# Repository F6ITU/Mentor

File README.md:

# Mentor

Kicad files

An Arduino based SSPA display controler for HPSDR/Hermes familly
This module controls 
- voltage
- current
- temperature
- VSWR/PWR
- cooling fan
- 4x40 lcd display
and shuts down the Bias current while beeping in case of dificulties

This board and the associated firmware have been developped by ON7EQ. 

http://www.qsl.net/on7eq/projects/arduino_sspa.htm

Some code modifications have been made by John Melton for 
the Hermes familly.

The design of this board uses the generic output names
used by all Hermes/Angelia boards and could directly be plugged 
on the Alexandrie control board

So far, NO SSPA and NO Reflectometer/Refl-fwd coupler have been
designed. A multipurpose 33dB Tandem Match coupler
is under development (for both VSWR/PWR measurement and 
predistorsion -aka "pure signal"- sampling)

Board's dimensions are oversized to fit the 5x10 and 10x10cm 
size of all board of the Hermes project under Kicad: 

AlexI2C

Alexandrie 

Alexiares_Coax_Out

Alexiares_HPF

Alexiares_LPF

Mentor(this one)

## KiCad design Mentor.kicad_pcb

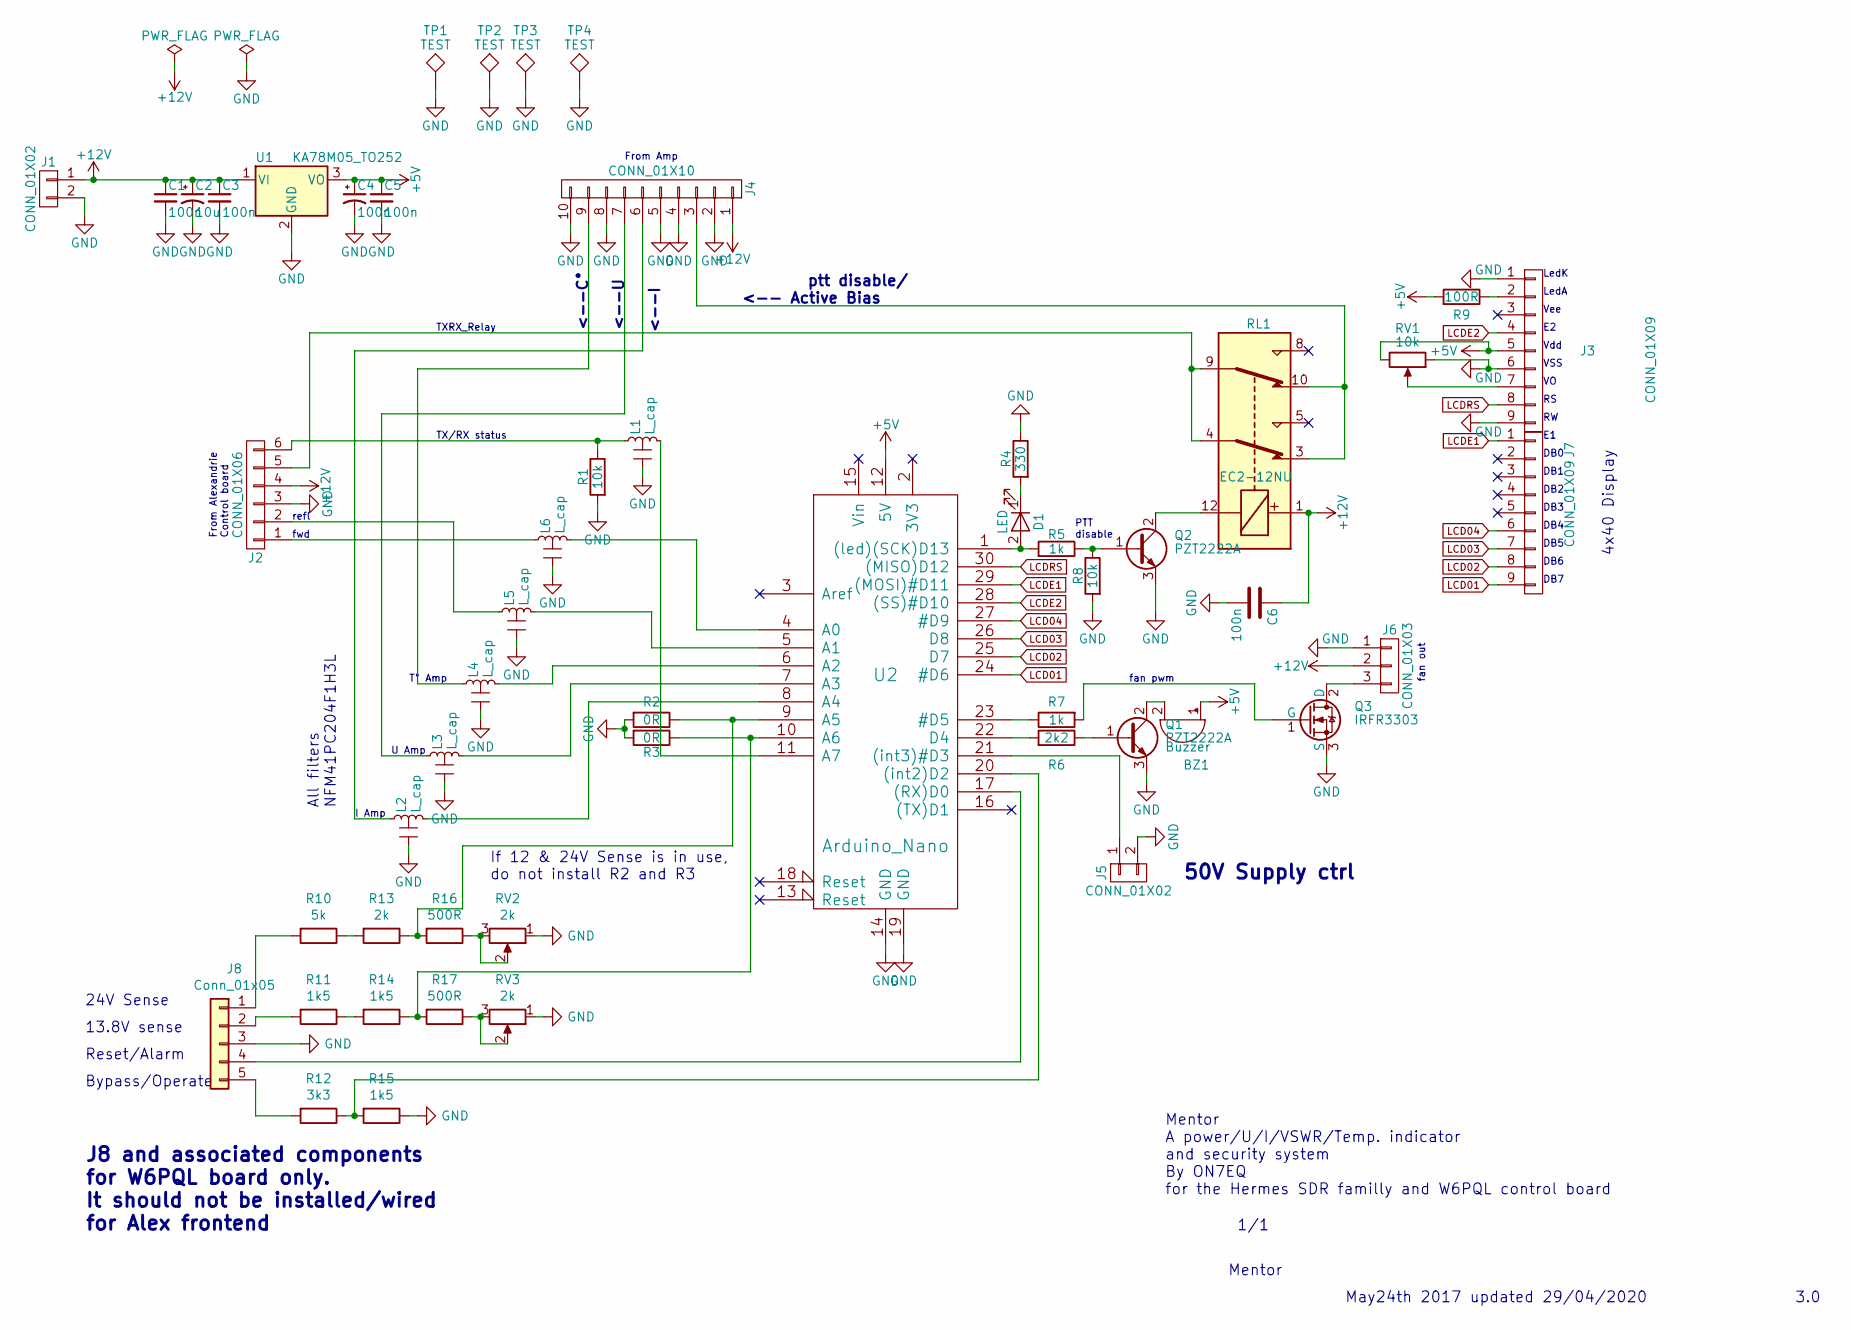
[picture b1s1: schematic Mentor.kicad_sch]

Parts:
BZ1: Buzzer; Buzzer_12x9.5RM7.6
C1, C3, C4, C5, C6: 100n; C_0805_2012Metric_Pad1.15x1.40mm_HandSolder
C2: 10u; CP_EIA-6032-28_Kemet-C_Pad2.25x2.35mm_HandSolder
D1: LED; D_0805_2012Metric_Pad1.15x1.40mm_HandSolder
J1, J5: CONN_01X02; kk100_22-23-2021
J2: CONN_01X06; kk100_22-23-2061
J3, J7: CONN_01X09; kk100_22-23-2091
J4: CONN_01X10; kk100_22-23-2101
J6: CONN_01X03; kk100_22-23-2031
J8: Conn_01x05; kk100_22-23-2051
L1, L2, L3, L4, L5, L6: L_cap; Ferrite_LC_NFM41P
Q1, Q2: PZT2222A; SOT-223
Q3: IRFR3303; TO-252-3_TabPin2
R1, R8: 10k; R_0805_2012Metric_Pad1.15x1.40mm_HandSolder
R2, R3: 0R; R_0805_2012Metric_Pad1.15x1.40mm_HandSolder
R4: 330; R_0805_2012Metric_Pad1.15x1.40mm_HandSolder
R5, R6: 1k; R_0805_2012Metric_Pad1.15x1.40mm_HandSolder
R7: 2k2; R_0805_2012Metric_Pad1.15x1.40mm_HandSolder
R9: 100R; R_0805_2012Metric_Pad1.15x1.40mm_HandSolder
R10: 5k; R_0805_2012Metric_Pad1.15x1.40mm_HandSolder
R11, R14, R15: 1k5; R_0805_2012Metric_Pad1.15x1.40mm_HandSolder
R12: 3k3; R_0805_2012Metric_Pad1.15x1.40mm_HandSolder
R13: 2k; R_0805_2012Metric_Pad1.15x1.40mm_HandSolder
R16, R17: 500R; R_0805_2012Metric_Pad1.15x1.40mm_HandSolder
RL1: EC2-12NU; THT_2_formC
RV1: 10k; Trimmer_3314G1_Handsoldering
RV2, RV3: 2k; Trimmer_3314G1_Handsoldering
TP1, TP2, TP3, TP4: TEST; MountingHole_3.5mm_Pad
U1: KA78M05_TO252; TO-252-3_TabPin2
U2: Arduino_Nano; arduino_nano

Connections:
+5V: BZ1.1 (-), C4.1, C5.1, J3.5, R9.2, RV1.3, U1.3 (VO), U2.12 (5V)
+12V: C1.1, C2.1, C3.1, C6.1, J1.1, J2.4, J4.1, J6.2, RL1.1, U1.1 (VI)
GND: C1.2, C2.2, C3.2, C4.2, C5.2, C6.2, J1.2, J2.3, J3.1, J3.6, J3.9, J4.2, J4.4, J4.5, J4.8, J4.10, J5.2, J6.1, J8.3, L1.2, L2.2, L3.2, L4.2, L5.2, L6.2, Q1.3 (E), Q2.3 (E), Q3.3 (S), R1.2, R2.2, R3.2, R4.1, R8.2, R15.1, RV1.1, RV2.1, RV3.1, TP1.1, TP2.1, TP3.1, TP4.1, U1.2 (GND), U2.14 (GND), U2.19 (GND)
LCD01: J7.9, U2.24 (#D6)
LCD02: J7.8, U2.25 (D7)
LCD03: J7.7, U2.26 (D8)
LCD04: J7.6, U2.27 (#D9)
LCDE1: J7.1, U2.29 ((MOSI)#D11)
LCDE2: J3.4, U2.28 ((SS)#D10)
LCDRS: J3.8, U2.30 ((MISO)D12)
unnamed: BZ1.2 (+), Q1.2 (C)
unnamed: D1.1 (K), R4.2
unnamed: D1.2 (A), R5.2, U2.1 ((led)(SCK)D13)
unnamed: J2.1, L6.1
unnamed: J2.2, L5.1
unnamed: J2.5, RL1.4, RL1.9
unnamed: J2.6, L1.1, R1.1
unnamed: J3.2, R9.1
unnamed: J3.7, RV1.2
unnamed: J4.3, RL1.3, RL1.10
unnamed: J4.6, L2.1
unnamed: J4.7, L3.1
unnamed: J4.9, L4.1
unnamed: J5.1, U2.21 ((int3)#D3)
unnamed: J6.3, Q3.2 (D)
unnamed: J8.1, R10.2
unnamed: J8.2, R11.2
unnamed: J8.4, U2.17 ((RX)D0)
unnamed: J8.5, R12.2
unnamed: L1.3, U2.11 (A7)
unnamed: L2.3, U2.8 (A4)
unnamed: L3.3, U2.7 (A3)
unnamed: L4.3, U2.6 (A2)
unnamed: L5.3, U2.5 (A1)
unnamed: L6.3, U2.4 (A0)
unnamed: Q1.1 (B), R7.1
unnamed: Q2.1 (B), R5.1, R8.1
unnamed: Q2.2 (C), RL1.12
unnamed: Q3.1 (G), R6.2
unnamed: R6.1, U2.23 (#D5)
unnamed: R7.2, U2.22 (D4)
unnamed: R10.1, R13.2
unnamed: R11.1, R14.2
unnamed: R12.1, R15.2, U2.20 ((int2)D2)
unnamed: R2.1, R13.1, R16.2, U2.9 (A5)
unnamed: R3.1, R14.1, R17.2, U2.10 (A6)
unnamed: R16.1, RV2.2, RV2.3
unnamed: R17.1, RV3.2, RV3.3

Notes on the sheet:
50V Supply ctrl
ptt disable/ <-- Active Bias
TXRX_Relay
24V Sense
<--I
T° Amp
Bypass/Operate
From Amp
DB6
<--U
Mentor A power/U/I/VSWR/Temp. indicator and security system By ON7EQ for the Hermes SDR familly and W6PQL control board
DB0
DB4
All filters NFM41PC204F1H3L
4x40 Display
DB5
May24th 2017 updated 29/04/2020
13.8V sense
3.0
Vdd
fwd
DB3
LedA
DB1
fan pwm
I Amp
J8 and associated components for W6PQL board only. It should not be installed/wired for Alex frontend
fan out
DB7
Reset/Alarm
From Alexandrie Control board
VSS
LedK
DB2
If 12 & 24V Sense is in use, do not install R2 and R3
U Amp
1/1
Vee
<--C°
TX/RX status

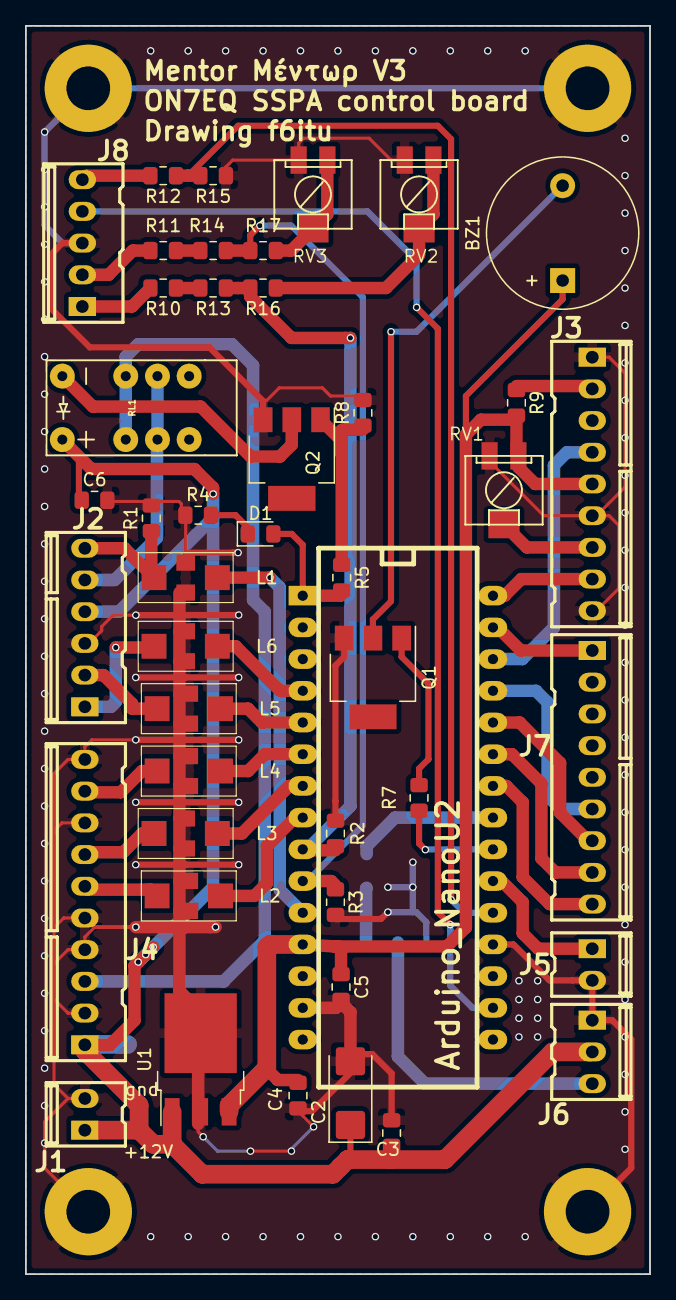
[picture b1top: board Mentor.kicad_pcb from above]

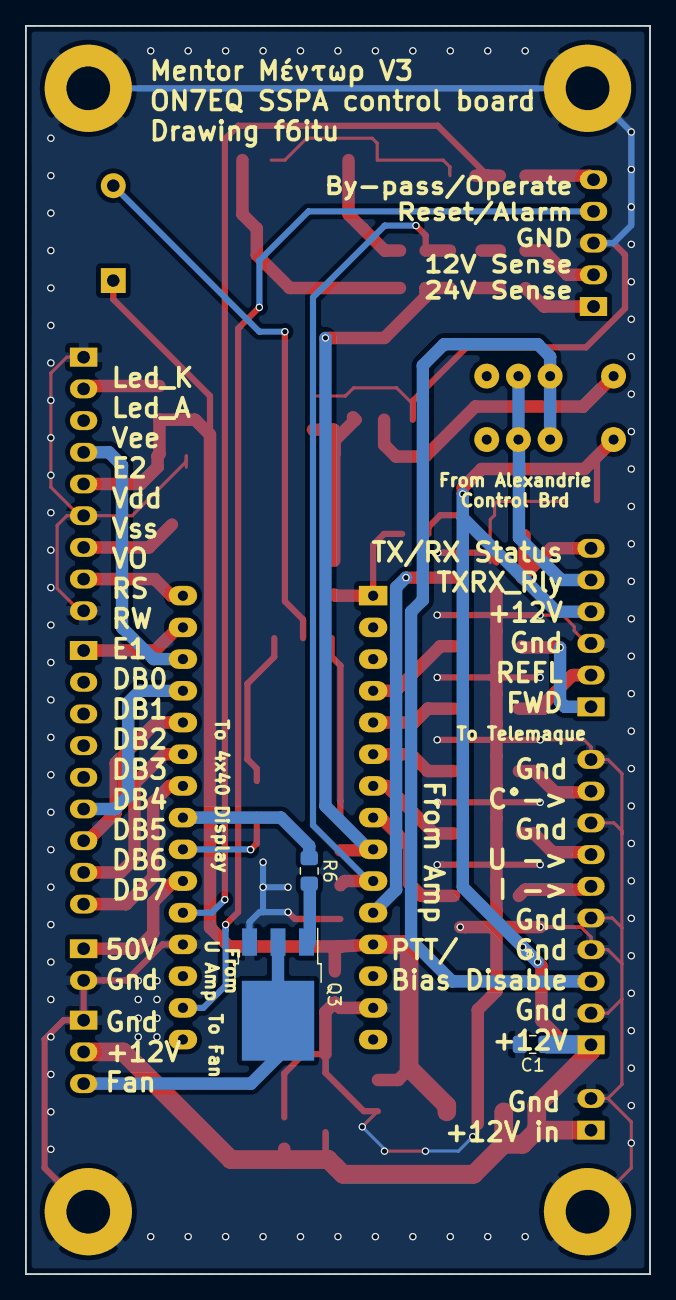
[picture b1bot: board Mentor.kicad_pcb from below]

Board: 2 copper layers, 50.0 x 100.0 mm, 52 parts (3 on the bottom side), 48 nets.

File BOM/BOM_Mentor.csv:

Component Count:,37,,,,
Ref,Value,Footprint,Datasheet,Manufacturer,Vendor
BZ1,Buzzer,Buzzers_Beepers:Buzzer_12x9.5RM7.6,,,
C1,100n,Capacitors_SMD:C_0805_HandSoldering,,,
C2,10u,Capacitors_Tantalum_SMD:CP_Tantalum_Case-C_EIA-6032-28_Hand,,,
C3,100n,Capacitors_SMD:C_0805_HandSoldering,,,
C4,100n,Capacitors_SMD:C_0805_HandSoldering,,,
C5,100n,Capacitors_SMD:C_0805_HandSoldering,,,
C6,100n,Capacitors_SMD:C_0805_HandSoldering,,,
D1,LED,Diodes_SMD:D_0805,LED,,
J1,CONN_01X02,conn_kk100:kk100_22-23-2021,,,
J2,CONN_01X06,conn_kk100:kk100_22-23-2061,,,
J3,CONN_01X09,conn_kk100:kk100_22-23-2091,,,
J4,CONN_01X10,conn_kk100:kk100_22-23-2101,,,
J5,CONN_01X02,conn_kk100:kk100_22-23-2021,,,
J6,CONN_01X03,conn_kk100:kk100_22-23-2031,,,
J7,CONN_01X09,conn_kk100:kk100_22-23-2091,,,
L1,L_cap,Ferrite_LC_NFM41P:Ferrite_LC_NFM41P,,,
L2,L_cap,Ferrite_LC_NFM41P:Ferrite_LC_NFM41P,,,
L3,L_cap,Ferrite_LC_NFM41P:Ferrite_LC_NFM41P,,,
L4,L_cap,Ferrite_LC_NFM41P:Ferrite_LC_NFM41P,,,
L5,L_cap,Ferrite_LC_NFM41P:Ferrite_LC_NFM41P,,,
L6,L_cap,Ferrite_LC_NFM41P:Ferrite_LC_NFM41P,,,
Q1,PZT2222A,TO_SOT_Packages_SMD:SOT-223,,,
Q2,PZT2222A,TO_SOT_Packages_SMD:SOT-223,,,
Q3,IRFR3303,TO_SOT_Packages_SMD:TO-252-3_TabPin2,,,
R1,10k,Resistors_SMD:R_0805_HandSoldering,,,
R2,0R,Resistors_SMD:R_0805_HandSoldering,,,
R3,0R,Resistors_SMD:R_0805_HandSoldering,,,
R4,330R,Resistors_SMD:R_0805_HandSoldering,,,
R5,1k,Resistors_SMD:R_0805_HandSoldering,,,
R6,1k,Resistors_SMD:R_0805_HandSoldering,,,
R7,2k2,Resistors_SMD:R_0805_HandSoldering,,,
R8,10k,Resistors_SMD:R_0805_HandSoldering,,,
R9,100R,Resistors_SMD:R_0805_HandSoldering,,,
RL1,EC2-12NU,2_Form_C_Relay:THT_2_formC,,,
RV1,10k,Trimmer_3314G1_Handsoldering:Trimmer_3314G1_Handsoldering,,,
U1,KA78M05_TO252,TO_SOT_Packages_SMD:TO-252-3_TabPin2,,,
U2,Arduino_Nano,arduino_nano:arduino_nano,,,

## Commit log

2017-05-24 Mentor display board for HPSDR first commit
2017-05-24 pdf view of Mentor's schematic
2017-05-24 Mentor Schematic, V1.0
2017-05-24 New schematic pdf file
2017-05-25 final schematic drawing
2017-05-27 Mentor pcb routed, minor errors fixed
2017-05-29 RTM, silmask to do
2017-06-12 carte de control V1.0
2017-07-29 add a THT relay, cleaning silk, shielding mask zone added
2017-11-01 RTM 1
2017-11-02 Readme cleaning, add 2 3D pictures
2017-11-02 Readme cleanup
2017-11-27 new ferrite footprint, minor routing changes
2017-11-27 deleted useless file
2017-12-01 RTM2, via, prototype picture, gerber added
2017-12-01 Silkmask comment added
2017-12-01 fixing some file names
2017-12-01 buzzer changed
2017-12-30 minor changes, Gerber and BOM added
2018-03-13 silk modified
2018-07-23 Mentor V2 RTM
2019-01-10 minor routing fix, V2 ok
2019-03-15 upgrade to kicad 5.x
2020-06-02 full W6PQL compatible version
2020-07-23 minor update on silk
2020-07-23 Mentor V3.0 W6PQL compatible
2026-06-28 new schematic for w6pql compatibility
